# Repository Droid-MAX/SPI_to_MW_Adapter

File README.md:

# SPI to MW Adapter
25 Series SPI Flash to 93c Series Microwire EEPROM ISP Adapter for CH341A Programmer.

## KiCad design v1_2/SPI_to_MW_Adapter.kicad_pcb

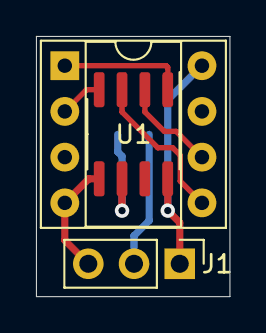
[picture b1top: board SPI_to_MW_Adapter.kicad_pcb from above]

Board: 2 copper layers, 10.7 x 14.5 mm, 4 parts (1 on the bottom side), 8 nets.

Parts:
J1: Conn_01x03; PinHeader_1x03_P2.54mm_Vertical
R1: 4.7K; R_0603_1608Metric_Pad1.05x0.95mm_HandSolder
U1: EEPROM-93C-SOIC-8; SOIC-8_3.9x4.9mm_P1.27mm
U2: SPI-25-SOIC-8; DIP-8_W7.62mm_Socket

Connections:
GND: J1.3, U1.5, U2.4
MISO: U1.4, U2.2
MOSI: U1.3, U2.5
unnamed: J1.2, R1.1
ORG: R1.2, U1.6
RST: U1.1, U2.1
SCK: U1.2, U2.6
VCC: J1.1, U1.8, U2.8

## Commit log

2021-07-07 pcb v1_2 details enhancement
2021-07-07 pcb v1_1 details enhancement
